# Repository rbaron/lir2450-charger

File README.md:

# LIR2450 Charger

An open source USB C battery charger for [LIR2450 Li-Ion coin cells](https://www.adafruit.com/product/1572).

This repo hosts the [KiCad](https://kicad.org/) project for the charger, which contains the schematic and printed circuit board layout so you can make your own.

# Tech Specs
* It uses Microchip's [MCP73831](https://www.microchip.com/wwwproducts/en/en024903) as the charge management controller
* 45mA charge current

# Bill of Materials (BOM)
The KiCad exported BOM is [here](kicad/lir2450-charger.csv).

# 3D Render

# License
The hardware and associated design files are released under the [Creative Commons CC BY-SA 4.0 license](https://creativecommons.org/licenses/by-sa/4.0/).

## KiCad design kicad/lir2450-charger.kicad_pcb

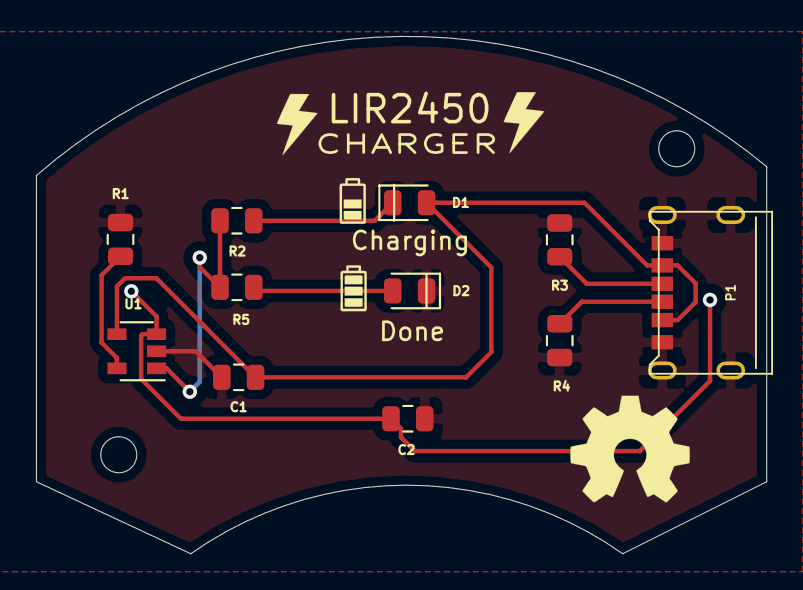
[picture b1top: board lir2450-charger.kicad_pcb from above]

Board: 2 copper layers, 40.6 x 28.7 mm, 12 parts (1 on the bottom side), 9 nets.

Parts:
BAT1: BS-7; BatteryHolder_Keystone_3008_1x2450
C1, C2: 4.7u; C_0805_2012Metric
D1: Red LED; LED_0805_2012Metric
D2: Green LED; LED_0805_2012Metric
P1: USB_C_Plug_USB2.0; TYPE-C-31-M-17
R1: 22k; R_0805_2012Metric
R2, R5: 220; R_0805_2012Metric
R3, R4: 5.1k; R_0805_2012Metric
U1: MCP73831-2-OT; SOT-23-5

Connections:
+5V: C1.1, D1.2, P1.A9, P1.B9, U1.4
GND: BAT1.Neg, C1.2, C2.2, D2.1, P1.A12, P1.B12, P1.S1, R1.2, R3.2, R4.2, U1.2
unnamed: BAT1.Pos, C2.1, U1.3
unnamed: D1.1, R2.1
unnamed: D2.2, R5.2
unnamed: P1.A5, R4.1
unnamed: P1.B5, R3.1
unnamed: R1.1, U1.5
unnamed: R2.2, R5.1, U1.1

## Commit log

2021-01-26 Adds green led & pcb icons
2021-02-05 Correct battery clip polarity
2021-02-06 Re-routes some tracks to avoid vias too close to the battery negative pad
2021-02-06 Adds proper battery footprint
2021-02-06 Plotted v1.0.0
2021-02-27 Updates R2 and R5 to 1k
2021-02-27 Adds a README.md and LICENSE
2021-02-27 Adds bill of materials to README.md
2024-02-09 Update to KiCad 7 and add MPNs for Seeedstudio fusion
